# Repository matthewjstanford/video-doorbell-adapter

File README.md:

# Doorbell Circuit

This document describes the doorbell circuit project, why it is needed, and how I propose to solve the problem.

## Current Configuration

As of the start of this project the configuration is:

* Two Ubiquiti Doorbell buttons deployed, one at the front door, one at the side door
* The transformer is 3016MT 16V 30VA Doorbell Transformer
* Both doorbells are configured to use the doorbell adapter
* Chime is Broan mechanical chime
* Doorbell buttons are connected to the network via WiFi

### Theory of Operation

This is my understanding of how the system operates.

1. 16VAC is supplied by the transformer to the chimes
1. The doorbell button is connected to the chimes so that the current being supplied to the doorbell button passes through the chime coil.
1. Under normal conditions (doorbell button is not pushed) the doorbell button can draw a small amount of current (how much?) and not activate the chime.
1. When the button is pressed a relay is closed that shorts the wires in the doorbell button. This causes a large amount of current to flow through the circuit, which activates the chime coil.
1. The doorbell buttons contain a small battery that allows it to handle surges of power draw without activating the chime.

## Problem

There are two distinct issues that I believe can both be solved with a single circuit design.

1. Under periods of sustained high load (on very cold days in the winter, when the battery is presumably underperforming) the additional current draw will cause the chimes to hum. The hum is the striker vibrating within the coil.
1. I would like to replace the cheap Broan mechanical chimes with a much nicer 8 tone chime. These type of chimes are not compatible with the Ubiquiti style doorbell buttons.
    1. The chime is connected directly to the transformer.
    1. Activating the chime requires shorting a pin to one of the transformer leads. Since current isn't flowing continually through the doorbell buttons it can't work with a video doorbell. (See wiring diagram below)
    1. Since the trigger mechanism is quite different (current draw vs shorting a pin) there is no direct way to get the Ubiquiti buttons to work with the new chime.
    
**Simple Chime Wiring**

**New Chime Wiring**

**UniFi Protect Wiring**

## Idea

The general idea is to design a circuit that will sit in between the chime and the doorbell buttons. This circuit will constantly supply the buttons with current, and then will detect when current draw exceeds a threshold. Upon triggering the circuit will close a relay for a short period of time. The relay pins can be used to activate the Broan style current chime, or can be used to short the pin on the new style chime.

## Goals

Net power consumption on this circuit is a bit of a concern. Each additional doorbell button adds more load. The 30VA transformer should be quite sufficient for two doorbells and either chime configuration. We should keep the power consumption of the new circuit to a minimum.

I'd like to do this without using a microcontroller of any sort. We should be able to design this circuit with discrete components and build adjustability into things with potentiometers.

## Unknowns

The Ubiquiti doorbell buttons come with "doorbell adapters" that go in parallel with the doorbell button itself. What do those do? Are the capacitors?

How many doorbell buttons/chime configurations should the design support? It should support at least two, but should it support 3 or 4? In case more are added?

## Circuit Design

* A current transformer will be used to measure the current that is sent to the doorbell button.
* The CT output will be rectified into DC (peak detector) and fed into an OpAmp.
* The OpAmp will be configured as an inverting comparator with a potentiometer on the Vref to make the threshold tunable.
* The output of the OpAmp will be fed into a 555 timer in Monostable configuration.
* The 555 timer output can directly actuate a relay.
* Most of the circuit design is DC, so we will need to convert from 16VAC to 12VDC. Since power consumption is a primary goal we should use a buck/switching power supply. A switching regulator like the LM2575 should work.

## Discrete Components

And a brief description of why these specific components were selected.

* OpAmp - LM358
    * I had a bunch of these from a previous project.
* Switching Regulator - LM2575-12WT
    * A switching regulator was selected for power efficiency sake, and 12V was selected because it is near the input AC voltage and also because we will need to operate relays. Lower voltage relays are available, but we want to manage current by using higher voltage.
* Current Transformer - CT05-1000
    * This was selected for its small form factor and turn ratio. 1000:1. A 1A primary current will result in 1mA secondary.
* Burden Resistor - 6k (1A (est)/1000 = 1mA; 6V (half of 12V) / 1mA = 6k)
    * Assuming the doorbell will consume 1A when the button is pressed, we want around a 6V voltage spike as input to the OpAmp.

## Things I learned along the way

* The LM358 is a "single source" OpAmp, so it does not need a virtual ground
* A simple peak detector, like what we are considering here, should work great for this application.
* A 16 VAC source (our Doorbell transformer) will be close to 21 VDC once rectified. Using LM2575 to regulate it to 12 V should be totally fine.
* A linear voltage regulator is sometimes required after a switching regulator like the LM2575. This is because the switching regulator can introduce noise. In our case, however, this likely won't be an issue. No linear regulator should be required.

## Sub Assemblies

### Power Supply

The power supply needs to convert 16VAC to 12VDC and it needs to be as efficient as possible. The switching regulator, LM2575-12WT, is not adjustable. It will output 12V.

The AC input is rectified using 4 1N4002 diodes and a 470uF smoothing capacitor. The remainder of the circuit is based on the LM2575-12WT data sheet. A 330uF capacitor, 330uH inductor, and a 1N5817 Schottky diode are being used. The diode does not need to be a Schottky diode, but we are using the 1N5817 in other parts of the circuit, so we're just using it here now.

### Current Sensor

I am using a 1000:1 current transformer with a 6k burden resistor. This means that a 1A current on the primary should result in 1mA current on the secondary. 1mA across a 6k resistor should result in 6V. However, the 6V signal will only last a few milliseconds as this is a sine wave.

#### Peak Detector

The peak detector is meant to capture that peak voltage and store it for a period of time. This is to provide the downstream 555 timer a strong signal.

V(t)=V<sub>0</sub>​e^−t/(RC)

* R=10 kΩ ( 1 x 10^4 )
* C=10 μF ( 1 x 10^-5 )
* Therefore RC = 1 x 10^-1 , or 0.1s or 100ms

In other words the voltage should decay 37% from the peak in around 100ms.

#### Amplifier

The operational amplifier is here to both invert the peak signal (take the voltage to zero) and to decouple the input signal from what we feed to the 555 timer.

### Timer

The timer portion of this circuit is necessary so that we can simulate a normal "press" of a doorbell button. This corresponds to the amount of time the relay stays closed.

The target should be around how long a doorbell button is normally held in the pressed position. But how long is that? Based on my own observation I suspect this is somewhere between 1/2 and 1 second.

As such I want the timer to stay activated somewhere in that range, but it should also be adjustable.

From the datasheet:

> For mono-stable operation, any of these timers can be connected as shown in Figure 9. If the output is low, application of a negative-going pulse to the trigger (TRIG) sets the flip-flop (Q goes low), drives the output high, and turns off Q1. Capacitor C then is charged through RA until the voltage across the capacitor reaches the threshold voltage of the threshold (THRES) input. If TRIG has returned to a high level, the output of the threshold comparator resets the flip-flop (Q goes high), drives the output low, and discharges C through Q1.

> Monostable operation is initiated when TRIG voltage falls below the trigger threshold. Once initiated, the sequence ends only if TRIG is high for at least 10 μs before the end of the timing interval. When the trigger is grounded, the comparator storage time can be as long as 10 μs, which limits the minimum monostable pulse width to 10 μs. Because of the threshold level and saturation voltage of Q1, the output pulse duration is approximately tw = 1.1RAC. Figure 11 is a plot of the time constant for various values of RA and C. The threshold levels and charge rates both are directly proportional to the supply voltage, VCC. The timing interval is, therefore, independent of the supply voltage, so long as the supply voltage is constant during the time interval.
Applying a negative-going trigger pulse simultaneously to RESET and TRIG during the timing interval discharges C and reinitiates the cycle, commencing on the positive edge of the reset pulse. The output is held low as long as the reset pulse is low. To prevent false triggering, when RESET is not used, it should be connected to VCC.

Using these charts we can see that with a 10uF capacitor and a 100k resistor (R<sub>A</sub> in diagram) we should be in the neighborhood of 1 second pulse duration. Varying the resistance with a 100k potentiometer will allow us to make adjustments to reduce the pulse duration.

## Breadboarding and testing

Several things got me along the way. Thankfully I was able to work through the issues.

This testing was done using a spare 120VAC -> 16VAC doorbell transformer that I purchased specifically for these tests.

1. Breadboard the 12V power supply
    1. Originally I had connected the diode backwards, which obviously won't work. Once that was corrected the power supply 
1. Breadboard the current sensor, and power it by the power supply
    1. I went through the current sensor first, then the peak detector, then the operational amplifier. I was able to confirm that a dead short on the 16VAC primary side of the CT resulted in around 5.6V across the burden resistor on the secondary. This is a little lower than I had anticipated, but it is fully in the range that should be workable.

    1. I had made a mistake when creating the schematic of the peak detector. I had originally had the 10uF capacitor in-line between the diode and the OpAmp. Obviously this won't work. Once I realized my mistake I switched that capacitor to go between the output and ground, and things look good.

    1. I could not get the OpAmp to work correctly on the bench. I had the LM358 wired up according to the data sheet & schematic, but it didn't seem to be doing anything. Additionally I could see that the non-inverting input pin was sitting around 11V, where it should be 4V (voltage divider from potentiometer). Turns out I did have the chip wired correctly, but I had a broken wire, so the device wasn't grounded. Once that wire was replaced everything behaved as expected.

1. Breadboard the timer & relay
    1. The timer circuit was verified on the bench and worked right out of the box. No issues were encountered here. I did confirm that the potentiometer would adjust the "press time". By default (middle of the range) the press time was around 0.7s.

1. Switch simple doorbell button to a video doorbell
    1. I don't have a spare video doorbell, so this step was skipped for now.

1. Design PCB in KiCad
    1. This was my first ever PCB layout & creation. I had good design intentions when starting the layout, but it quickly devolved into chaos. I've come to realize that intuition is a key component to good design. That probably applies to all disciplines.
    1. I believe what I ended up with is a functional PCB, but it isn't pretty. Because this is my first ever layout, I'm running with it. I fairly certain if I were to start with a clean sheet and do it all again I would end up with a much better product. If it turns out there are any issues with the PCB then I'll just start over.

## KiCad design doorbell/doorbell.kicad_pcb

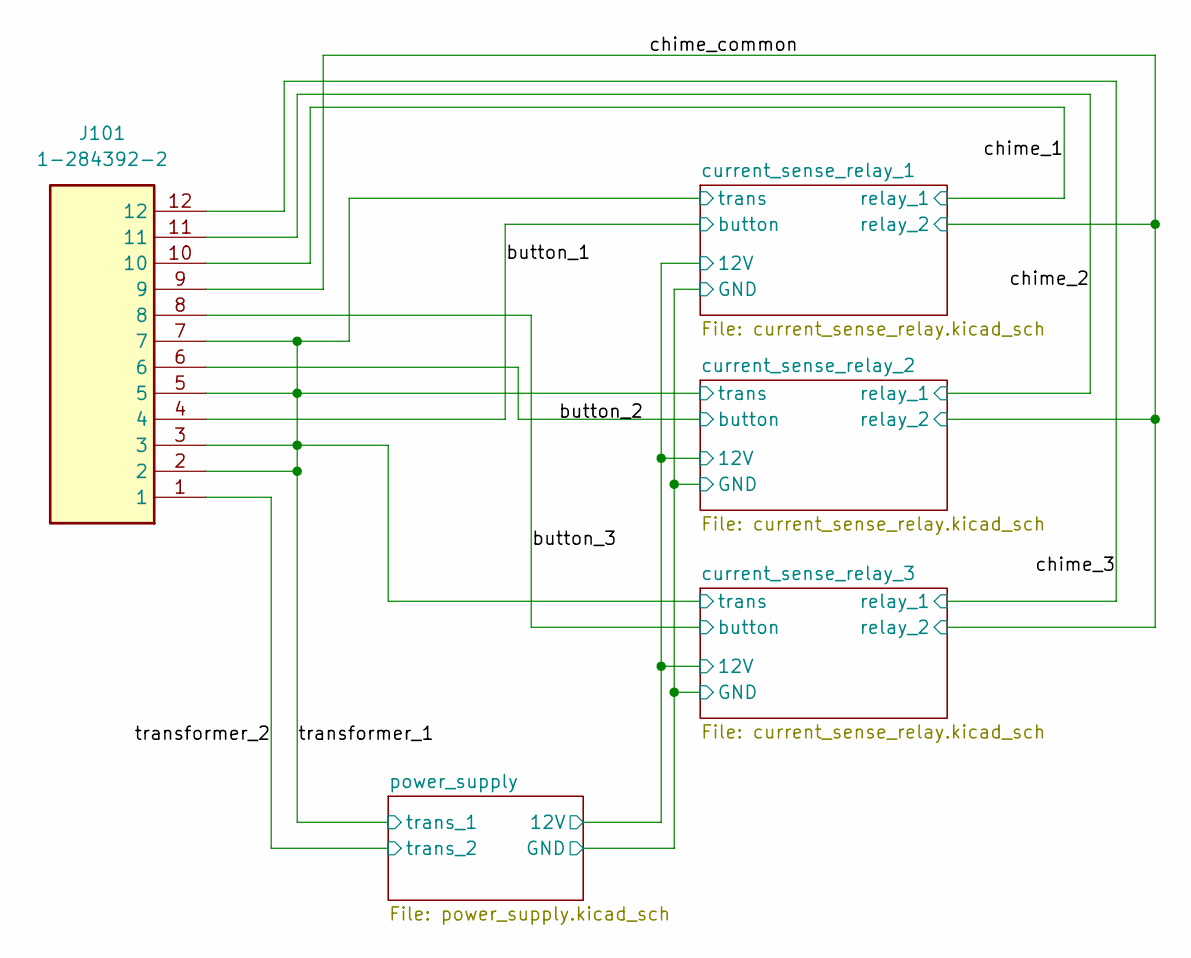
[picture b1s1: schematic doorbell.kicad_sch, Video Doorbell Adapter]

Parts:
J101: 1-284392-2; SHDR12W100P0X381_1X12_4572X820X1280P; Mouser Part Number 571-1-284392-2

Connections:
/button_1: J101.4; also elsewhere on the board
/button_3: J101.8; also elsewhere on the board
/chime_1: J101.10; also elsewhere on the board
/chime_2: J101.11; also elsewhere on the board
/chime_3: J101.12; also elsewhere on the board
/chime_common: J101.9; also elsewhere on the board
/current_sense_relay_2/button: J101.6; also elsewhere on the board
/transformer_1: J101.2, J101.3, J101.5, J101.7; also elsewhere on the board
/transformer_2: J101.1; also elsewhere on the board

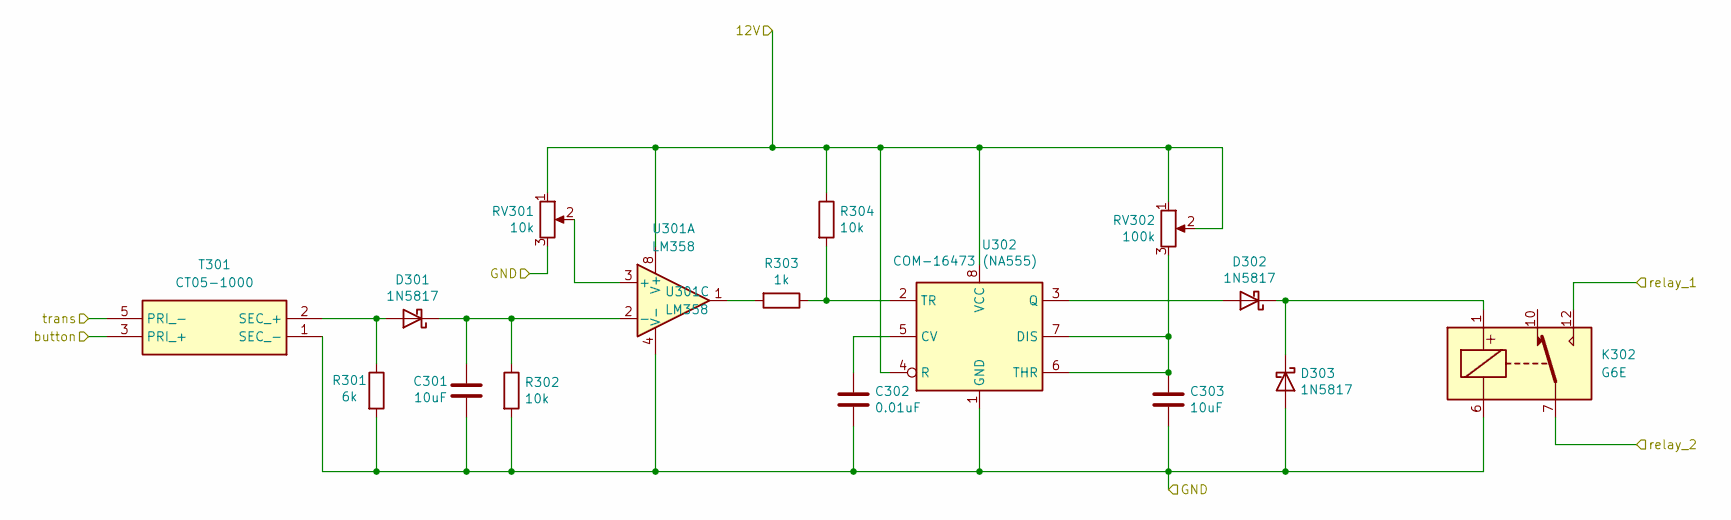
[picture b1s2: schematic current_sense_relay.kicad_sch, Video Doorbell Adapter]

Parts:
C301, C303: 10uF; C_Disc_D5.0mm_W2.5mm_P5.00mm
C302: 0.01uF; C_Disc_D5.0mm_W2.5mm_P5.00mm
D301, D302, D303: 1N5817; D_DO-41_SOD81_P10.16mm_Horizontal
K302: G6E; Relay_SPDT_Omron_G6E
R301: 6k; R_Axial_DIN0411_L9.9mm_D3.6mm_P15.24mm_Horizontal
R302, R304: 10k; R_Axial_DIN0207_L6.3mm_D2.5mm_P10.16mm_Horizontal
R303: 1k; R_Axial_DIN0207_L6.3mm_D2.5mm_P10.16mm_Horizontal
RV301: 10k; Potentiometer_Vishay_T93YA_Vertical
RV302: 100k; Potentiometer_Vishay_T73YP_Vertical
T301: CT05-1000; CT051000; Mouser Part Number 911-CT05-1000
U301: LM358; DIP-8_W7.62mm
U302: COM-16473 (NA555); DIP-8_W7.62mm

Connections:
/button_1: T301.3 (PRI_+); also elsewhere on the board
/chime_1: K302.12; also elsewhere on the board
/chime_common: K302.7; also elsewhere on the board
/current_sense_relay_1/12V: R304.1, RV301.1, RV302.1, RV302.2, U301.8 (V+), U302.4 (R), U302.8 (VCC); also elsewhere on the board
/current_sense_relay_1/GND: C301.2, C302.2, C303.2, D303.2 (A), K302.6, R301.2, R302.2, RV301.3, T301.1 (SEC_-), U301.4 (V-), U302.1 (GND); also elsewhere on the board
/transformer_1: T301.5 (PRI_-); also elsewhere on the board
unnamed: D301.2 (A), R301.1, T301.2 (SEC_+)
unnamed: C301.1, D301.1 (K), R302.1, U301.2 (-)
unnamed: D302.2 (A), U302.3 (Q)
unnamed: D302.1 (K), D303.1 (K), K302.1
unnamed: R303.2, U301.1
unnamed: RV301.2, U301.3 (+)
unnamed: C302.1, U302.5 (CV)
unnamed: C303.1, RV302.3, U302.6 (THR), U302.7 (DIS)
unnamed: R303.1, R304.2, U302.2 (TR)

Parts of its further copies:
C401, C403, C501, C503: 10uF; C_Disc_D5.0mm_W2.5mm_P5.00mm
C402, C502: 0.01uF; C_Disc_D5.0mm_W2.5mm_P5.00mm
D401, D402, D403, D501, D502, D503: 1N5817; D_DO-41_SOD81_P10.16mm_Horizontal
K402, K502: G6E; Relay_SPDT_Omron_G6E
R401, R501: 6k; R_Axial_DIN0411_L9.9mm_D3.6mm_P15.24mm_Horizontal
R402, R404, R502, R504: 10k; R_Axial_DIN0207_L6.3mm_D2.5mm_P10.16mm_Horizontal
R403, R503: 1k; R_Axial_DIN0207_L6.3mm_D2.5mm_P10.16mm_Horizontal
RV401, RV501: 10k; Potentiometer_Vishay_T93YA_Vertical
RV402, RV502: 100k; Potentiometer_Vishay_T73YP_Vertical
T401, T501: CT05-1000; CT051000; Mouser Part Number 911-CT05-1000
U401, U501: LM358; DIP-8_W7.62mm
U402, U502: COM-16473 (NA555); DIP-8_W7.62mm

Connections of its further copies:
/button_3: T501.3 (PRI_+); also elsewhere on the board
/chime_2: K402.12; also elsewhere on the board
/chime_3: K502.12; also elsewhere on the board
/chime_common: K402.7, K502.7; also elsewhere on the board
/current_sense_relay_1/12V: R404.1, R504.1, RV401.1, RV402.1, RV402.2, RV501.1, RV502.1, RV502.2, U401.8 (V+), U402.4 (R), U402.8 (VCC), U501.8 (V+), U502.4 (R), U502.8 (VCC); also elsewhere on the board
/current_sense_relay_1/GND: C401.2, C402.2, C403.2, C501.2, C502.2, C503.2, D403.2 (A), D503.2 (A), K402.6, K502.6, R401.2, R402.2, R501.2, R502.2, RV401.3, RV501.3, T401.1 (SEC_-), T501.1 (SEC_-), U401.4 (V-), U402.1 (GND), U501.4 (V-), U502.1 (GND); also elsewhere on the board
/current_sense_relay_2/button: T401.3 (PRI_+); also elsewhere on the board
/transformer_1: T401.5 (PRI_-), T501.5 (PRI_-); also elsewhere on the board
unnamed: D401.2 (A), R401.1, T401.2 (SEC_+)
unnamed: C401.1, D401.1 (K), R402.1, U401.2 (-)
unnamed: D402.2 (A), U402.3 (Q)
unnamed: D402.1 (K), D403.1 (K), K402.1
unnamed: D501.2 (A), R501.1, T501.2 (SEC_+)
unnamed: C501.1, D501.1 (K), R502.1, U501.2 (-)
unnamed: D502.2 (A), U502.3 (Q)
unnamed: D502.1 (K), D503.1 (K), K502.1
unnamed: R403.2, U401.1
unnamed: R503.2, U501.1
unnamed: RV401.2, U401.3 (+)
unnamed: C402.1, U402.5 (CV)
unnamed: C403.1, RV402.3, U402.6 (THR), U402.7 (DIS)
unnamed: R403.1, R404.2, U402.2 (TR)
unnamed: RV501.2, U501.3 (+)
unnamed: C502.1, U502.5 (CV)
unnamed: C503.1, RV502.3, U502.6 (THR), U502.7 (DIS)
unnamed: R503.1, R504.2, U502.2 (TR)

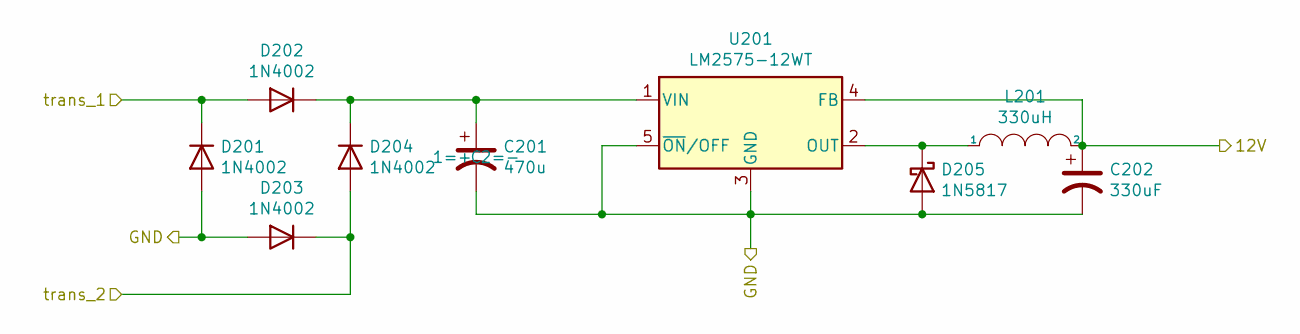
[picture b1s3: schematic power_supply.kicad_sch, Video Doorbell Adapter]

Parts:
C201: 470u; CP_Radial_D10.0mm_P5.00mm
C202: 330uF; CP_Radial_D10.0mm_P5.00mm
D201, D202, D203, D204: 1N4002; D_DO-41_SOD81_P10.16mm_Horizontal
D205: 1N5817; D_DO-41_SOD81_P10.16mm_Horizontal
L201: 330uH; L_Toroid_Vertical_L24.6mm_W15.5mm_P11.44mm_Pulse_KM-4
U201: LM2575-12WT; TO-262-5_Vertical

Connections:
/current_sense_relay_1/12V: C202.1, L201.2, U201.4 (FB); also elsewhere on the board
/current_sense_relay_1/GND: C201.2, C202.2, D201.2 (A), D203.2 (A), D205.2 (A), U201.3 (GND), U201.5 (~ON/OFF); also elsewhere on the board
/transformer_1: D201.1 (K), D202.2 (A); also elsewhere on the board
/transformer_2: D203.1 (K), D204.2 (A); also elsewhere on the board
unnamed: C201.1, D202.1 (K), D204.1 (K), U201.1 (VIN)
unnamed: D205.1 (K), L201.1, U201.2 (OUT)

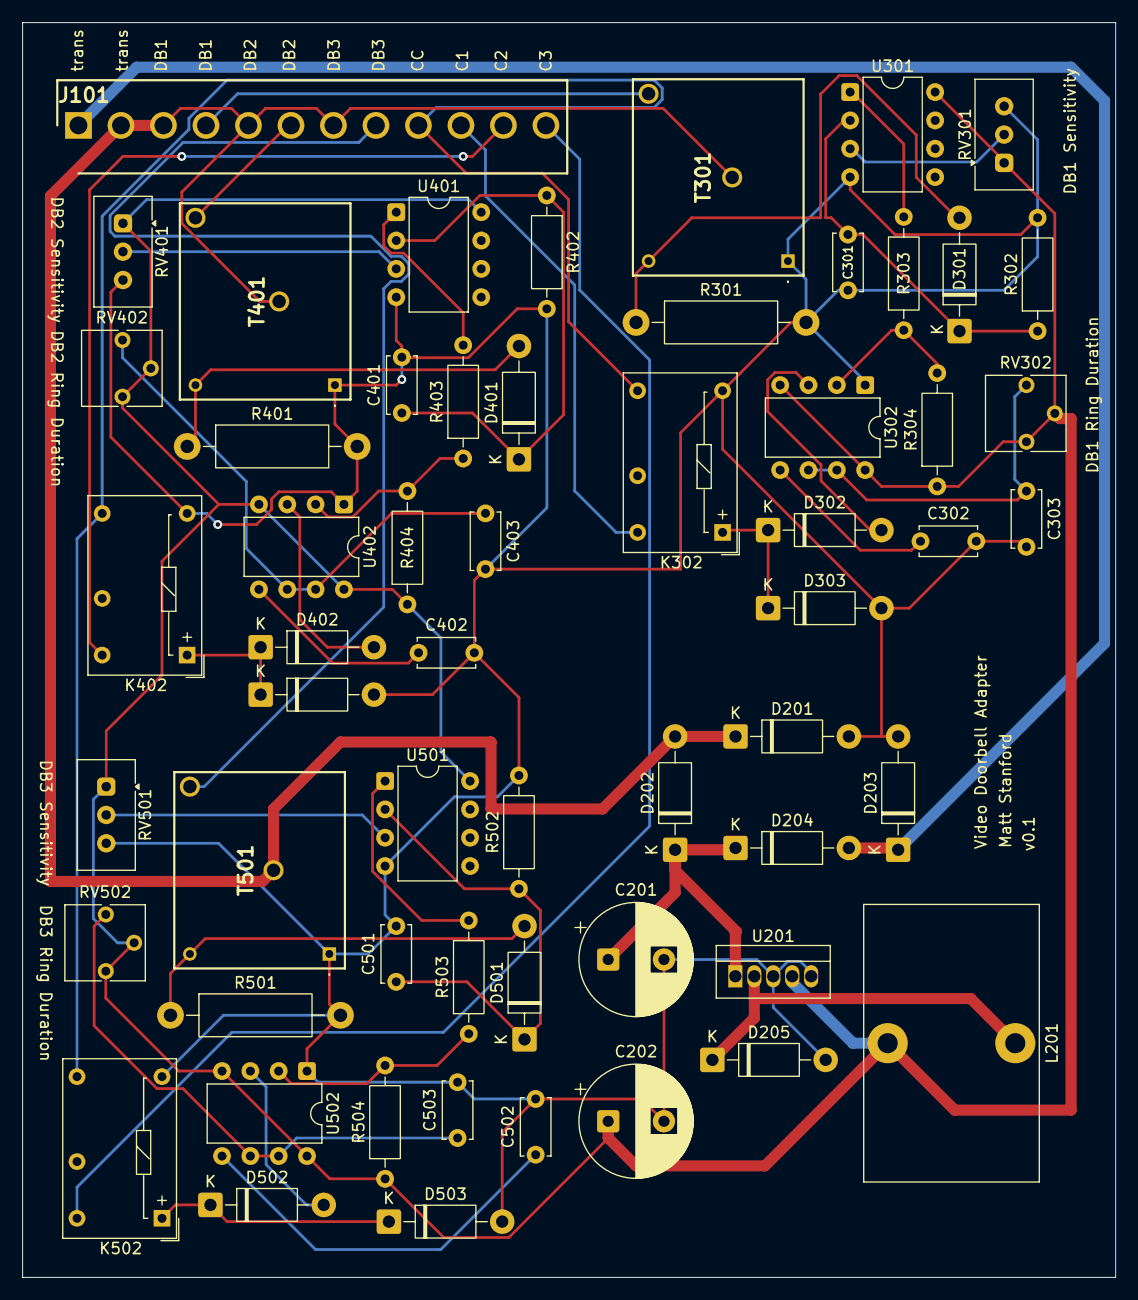
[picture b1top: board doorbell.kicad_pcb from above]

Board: 2 copper layers, 98.0 x 112.5 mm, 58 parts (0 on the bottom side), 40 nets.

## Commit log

2025-08-05 Initial checkin. Adding README and schematic
2025-08-05 Adding PDF of schematic
2025-08-11 Adding some diagrams for the README
2025-08-11 Adding reference to image
2025-08-11 Adding more images
2025-08-11 Adding refs to images
2025-08-22 v0.1.3 - adjusted some diodes. Updated readme
2025-08-24 Updating readme and peak detector
2025-08-26 Updating schematic to include all three CTs
2025-08-28 Updating schematic to be multiple sheets, including gerber files for PCB, updating readme
2025-08-28 Adding testing screenshots
2025-08-28 Adding image of PCB
